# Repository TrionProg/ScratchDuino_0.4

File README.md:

# ScratchDuino_0.4

===============

#Centent

##Cartridge
##Roboplatform board

##Sensors
###Light
###Line
###Touch
###Eye
##

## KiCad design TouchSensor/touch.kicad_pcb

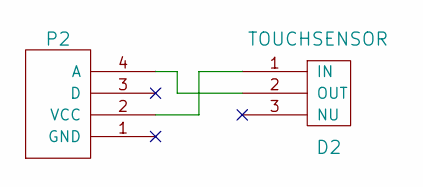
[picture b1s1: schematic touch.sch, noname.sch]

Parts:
D2: TOUCHSENSOR
P2: SENSOR

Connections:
unnamed: D2.1 (IN), P2.2 (VCC)
unnamed: D2.2 (OUT), P2.4 (A)

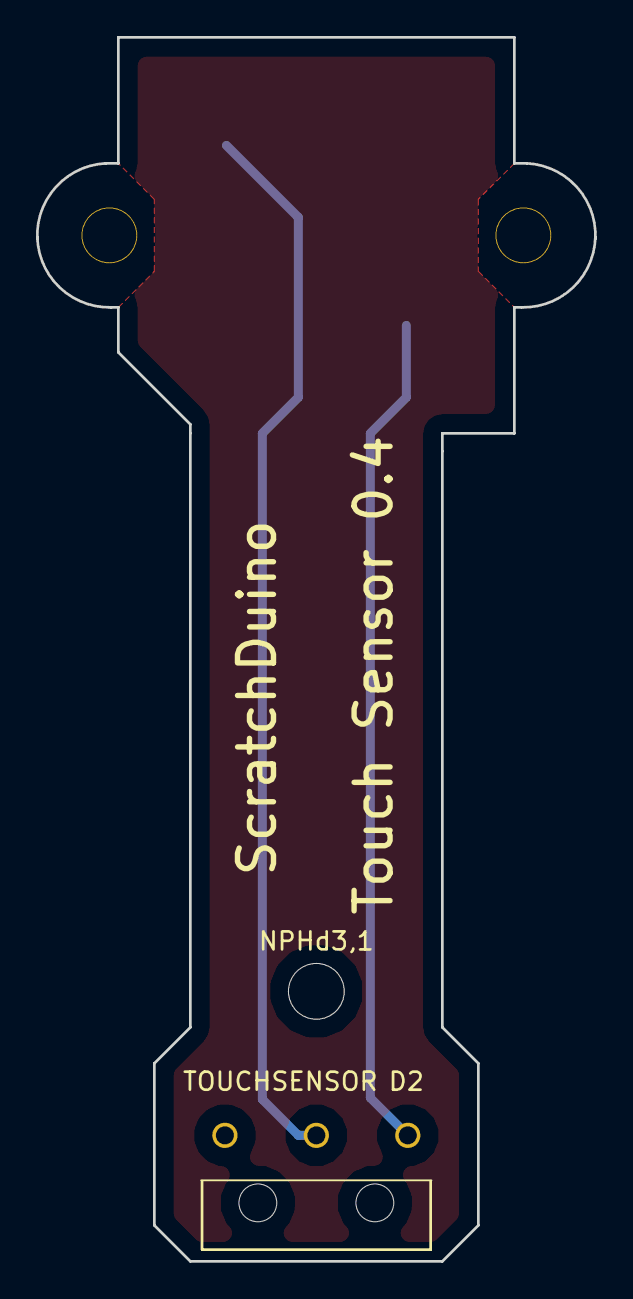
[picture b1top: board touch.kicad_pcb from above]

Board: 2 copper layers, 31.0 x 68.0 mm, 3 parts (1 on the bottom side), 2 nets.

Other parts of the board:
NPHd3,1: NPHd3,1

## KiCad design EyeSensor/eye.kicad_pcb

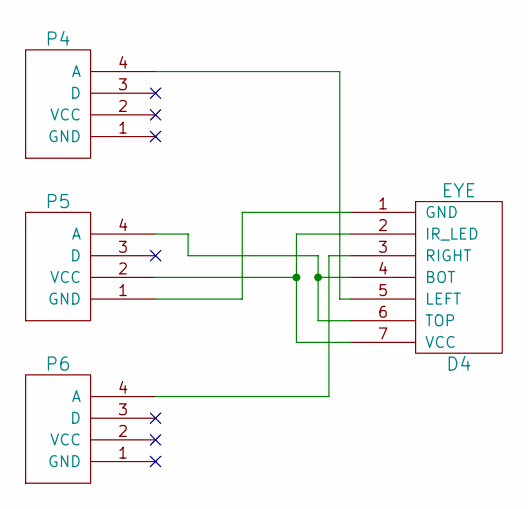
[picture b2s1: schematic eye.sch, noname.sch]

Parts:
D4: EYE
P4, P5, P6: SENSOR

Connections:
unnamed: D4.3 (RIGHT), P6.4 (A)
unnamed: D4.4 (BOT), D4.6 (TOP), P5.4 (A)
unnamed: D4.5 (LEFT), P4.4 (A)
unnamed: D4.1 (GND), P5.1 (GND)
unnamed: D4.2 (IR_LED), D4.7 (VCC), P5.2 (VCC)

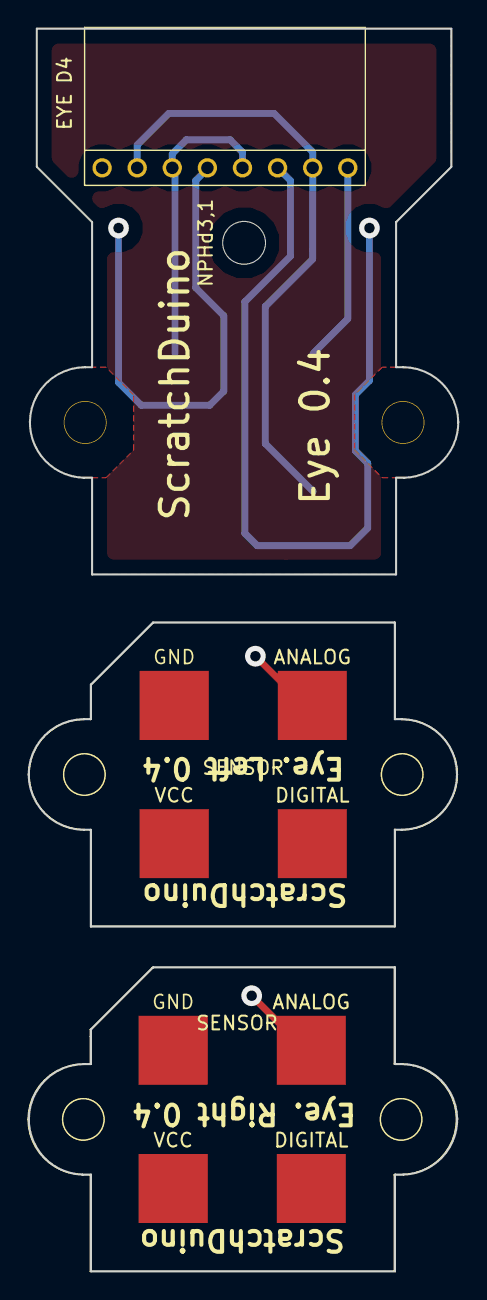
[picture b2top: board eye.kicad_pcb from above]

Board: 2 copper layers, 31.1 x 89.9 mm, 5 parts (1 on the bottom side), 5 nets.

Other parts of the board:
NPHd3,1: NPHd3,1

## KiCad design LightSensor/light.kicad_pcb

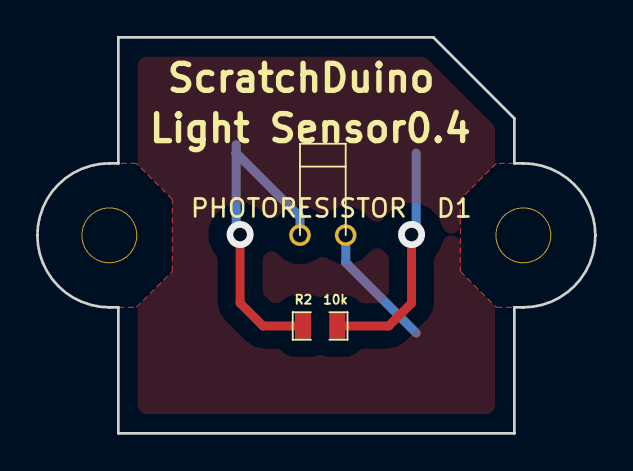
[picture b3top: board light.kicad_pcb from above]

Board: 2 copper layers, 31.0 x 22.0 mm, 3 parts (1 on the bottom side), 3 nets.

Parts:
D1: PHOTORESISTOR
P3: SENSOR
R2: 10k; SMD0805

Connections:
unnamed: D1.1, P3.2
unnamed: D1.2, P3.4, R2.2
unnamed: P3.1, R2.1

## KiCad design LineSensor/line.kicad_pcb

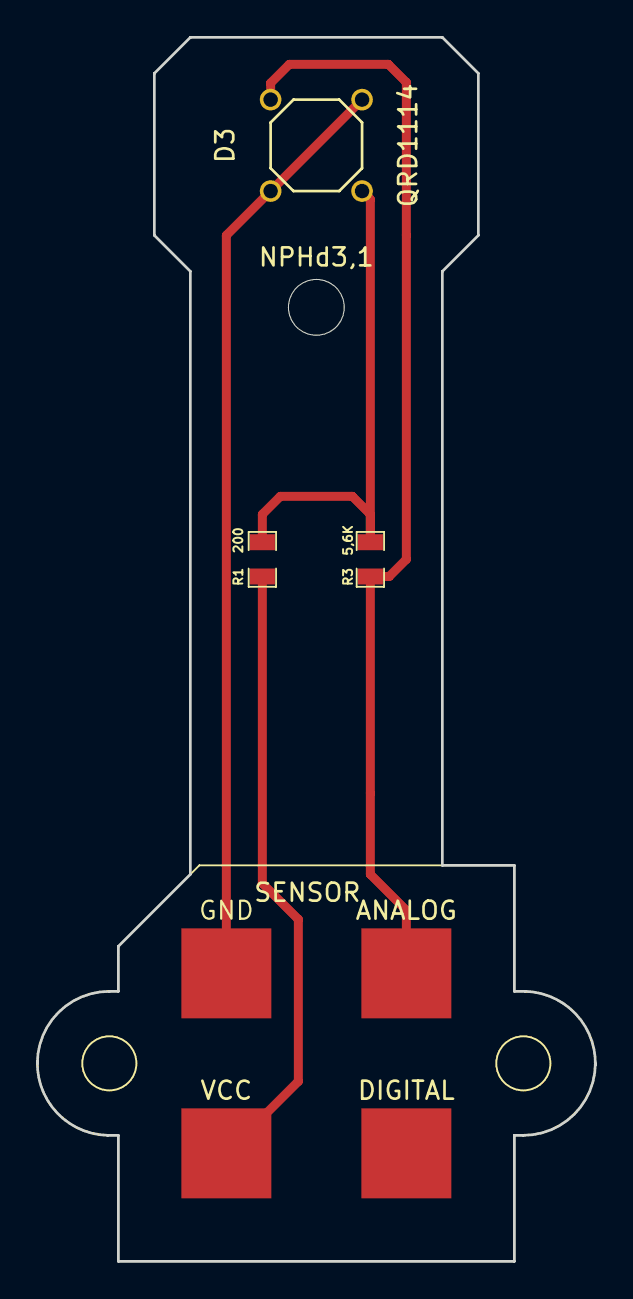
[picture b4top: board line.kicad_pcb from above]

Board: 2 copper layers, 31.0 x 68.0 mm, 5 parts (0 on the bottom side), 4 nets.

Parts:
D3: QRD1114
NPHd3,1: NPHd3,1
P1: SENSOR
R1: 200; SMD0805
R3: 5,6K; SMD0805

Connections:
unnamed: D3.2, D3.4, P1.1
unnamed: D3.3, P1.4, R3.2
unnamed: D3.1, R1.2, R3.1
unnamed: P1.2, R1.1

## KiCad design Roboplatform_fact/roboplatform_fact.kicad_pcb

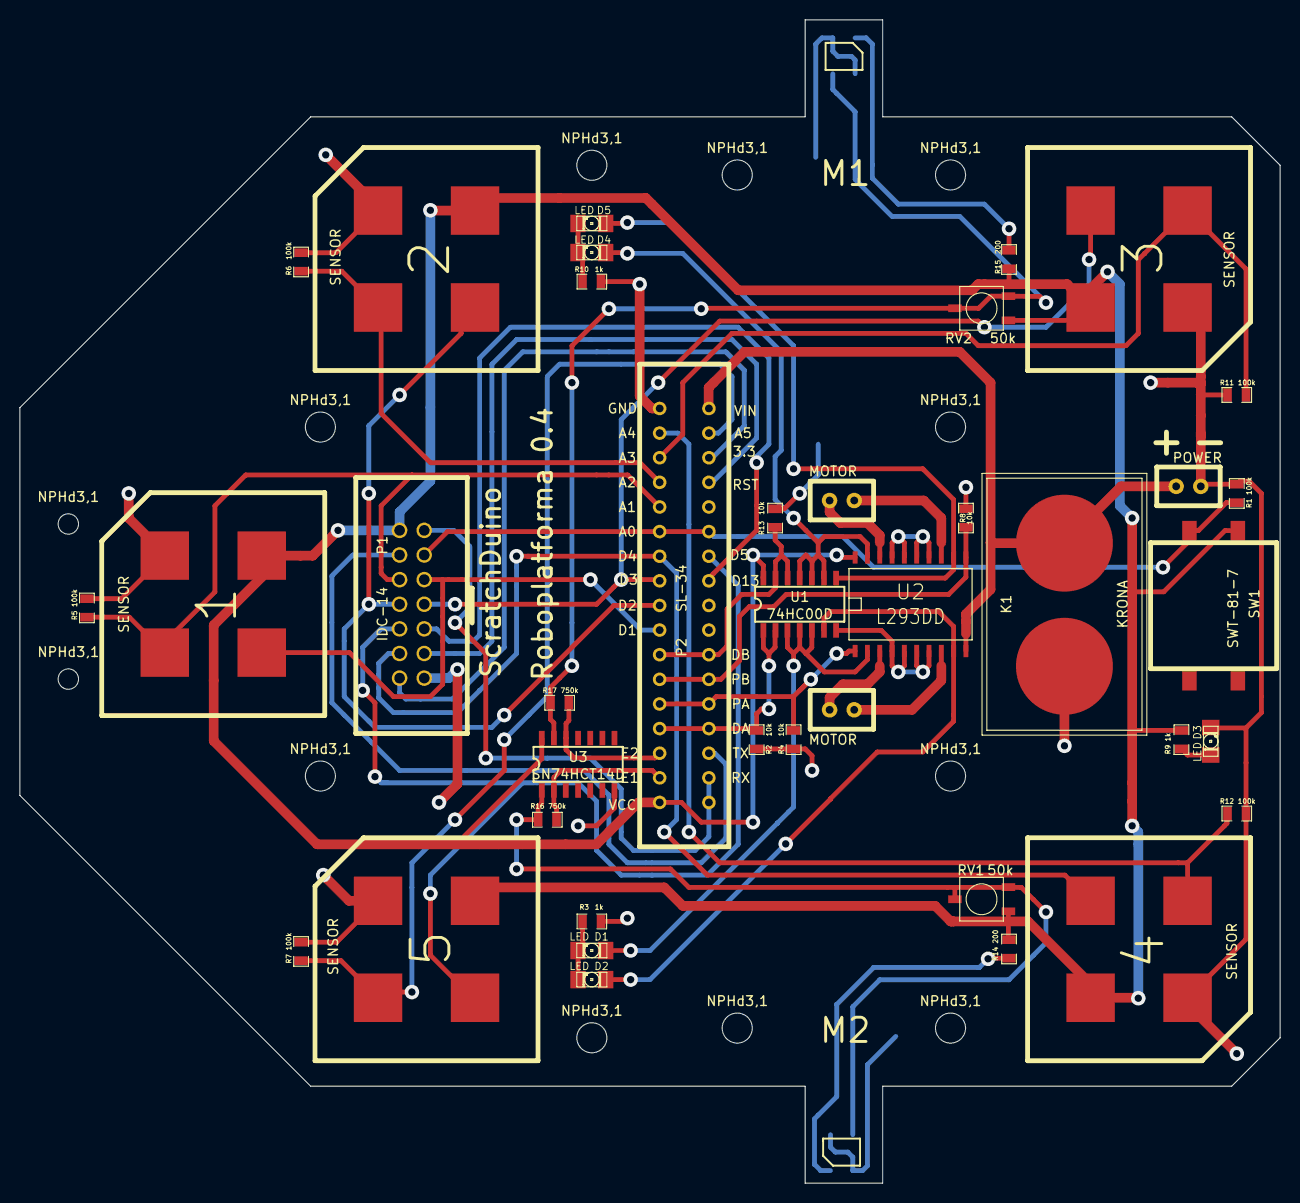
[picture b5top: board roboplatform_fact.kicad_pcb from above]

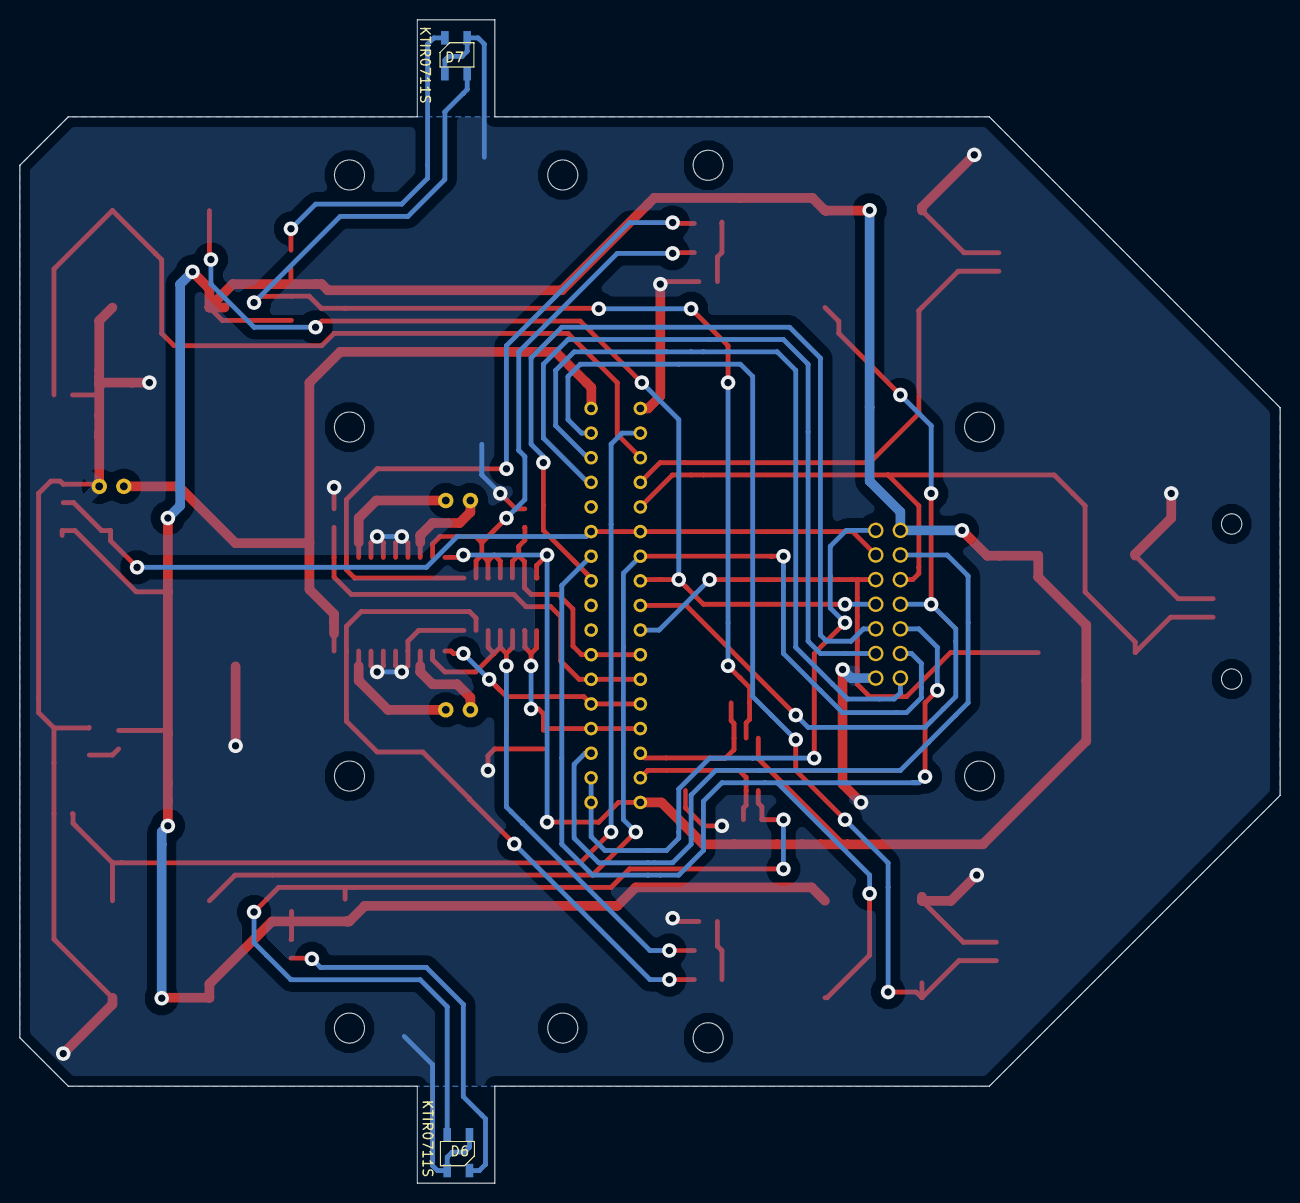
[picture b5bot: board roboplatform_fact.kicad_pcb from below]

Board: 2 copper layers, 130.0 x 120.0 mm, 53 parts (2 on the bottom side), 40 nets.

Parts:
D1, D2, D3, D4, D5: LED; LED-1206
D6, D7: KTIR0711S
K1: KRONA
NPHd3,1, NPHd3,1#2, NPHd3,1#3, NPHd3,1#4, NPHd3,1#5, NPHd3,1#6, NPHd3,1#7, NPHd3,1#8, NPHd3,1#9, NPHd3,1#10: NPHd3,1
NPHd3,1#11, NPHd3,1#12: NPHd2,1
P1: IDC-14; IDC-14M_SOCKET
P2: SL-34; SL-34_SOCKET
P3, P12: MOTOR
P6, P7, P8, P10, P11: SENSOR; SENSOR_SOCKET
P9: POWER
R1, R5, R6, R7, R11, R12: 100k; SMD0805
R2, R4, R8, R13: 10k; SMD0805
R3, R9, R10: 1k; SMD0805
R14, R15: 200; SMD0805
R16, R17: 750k; SMD0805
RV1, RV2: 50k; 3314G-1-503E
SW1: SWT-81-7
U1: 74HC00D; SOIC-14
U2: L293DD; SO20
U3: SN74HCT14D; SOIC-14

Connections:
A1: P1.10, P2.5, P6.4, R5.1
A2: P2.4, P7.4, R6.1
A3: P2.3, P10.4, R11.1
A4: P2.2, P11.4, R12.1
A5: P2.33, P8.4, R7.1
D1: P1.9, P2.10, P6.3
D2: P1.8, P2.9, P7.3
D3: P1.7, P2.8, P10.3
D4: P1.4, P2.7, P11.3
D5: P1.6, P2.28, P8.3
DIR_A: P2.14, P2.21, R2.1, U1.1, U1.2
DIR_B: P2.11, P2.24, R13.1, U1.12, U1.13
ENC1: P2.16, R16.1, U3.2
ENC2: P2.15, R17.2, U3.12
GND: D3.2, D6.2, D6.4, D7.2, D7.4, K1.2, P1.1, P2.1, P6.1, P7.1, P8.1, P9.2, P10.1, P11.1, R1.2, R2.2, R3.1, R4.1, R5.2, R6.2, R7.2, R8.2, R10.1, R11.2, R12.2, R13.2, U1.7, U2.4, U2.5, U2.6, U2.7, U2.14, U2.15, U2.16, U2.17, U3.7
unnamed: P1.12, P2.20
unnamed: P1.13, P2.18, P2.19
unnamed: P1.3, P2.31
unnamed: P1.2, P2.32
unnamed: P3.2, U2.3
unnamed: P1.11, P2.6, P2.29, R1.1, SW1.1
unnamed: P3.1, U2.8
unnamed: D1.1, U1.3, U1.4, U1.5, U2.2
unnamed: P12.1, U2.13
unnamed: P12.2, U2.18
unnamed: D4.1, U1.9, U1.10, U1.11, U2.19
unnamed: D7.1, R15.2
unnamed: D6.1, R14.2
unnamed: D2.1, U1.6, U2.9
unnamed: P1.5, P2.27
unnamed: D3.1, R9.2
unnamed: D7.3, R17.1, RV2.1, RV2.2, U3.13
unnamed: D6.3, R16.2, RV1.1, RV1.2, U3.1
unnamed: D1.2, D2.2, R3.2
unnamed: D4.2, D5.2, R10.2
unnamed: D5.1, U1.8, U2.12
PWM_A: P2.13, P2.22, R4.2, U2.1
PWM_B: P2.12, P2.23, R8.1, U2.11
VCC: P1.14, P2.17, P6.2, P7.2, P8.2, P10.2, P11.2, R9.1, R14.1, R15.1, RV1.3, RV2.3, SW1.2, U1.14, U2.20, U3.14
V_IN: K1.1, P2.34, P9.1, U2.10

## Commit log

2015-08-28 Alpha 0.1 boards only
